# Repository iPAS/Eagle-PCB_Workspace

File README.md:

# Eagle-PCB Project Files

Sorry for inconvenience, I will make a description and index in near future.

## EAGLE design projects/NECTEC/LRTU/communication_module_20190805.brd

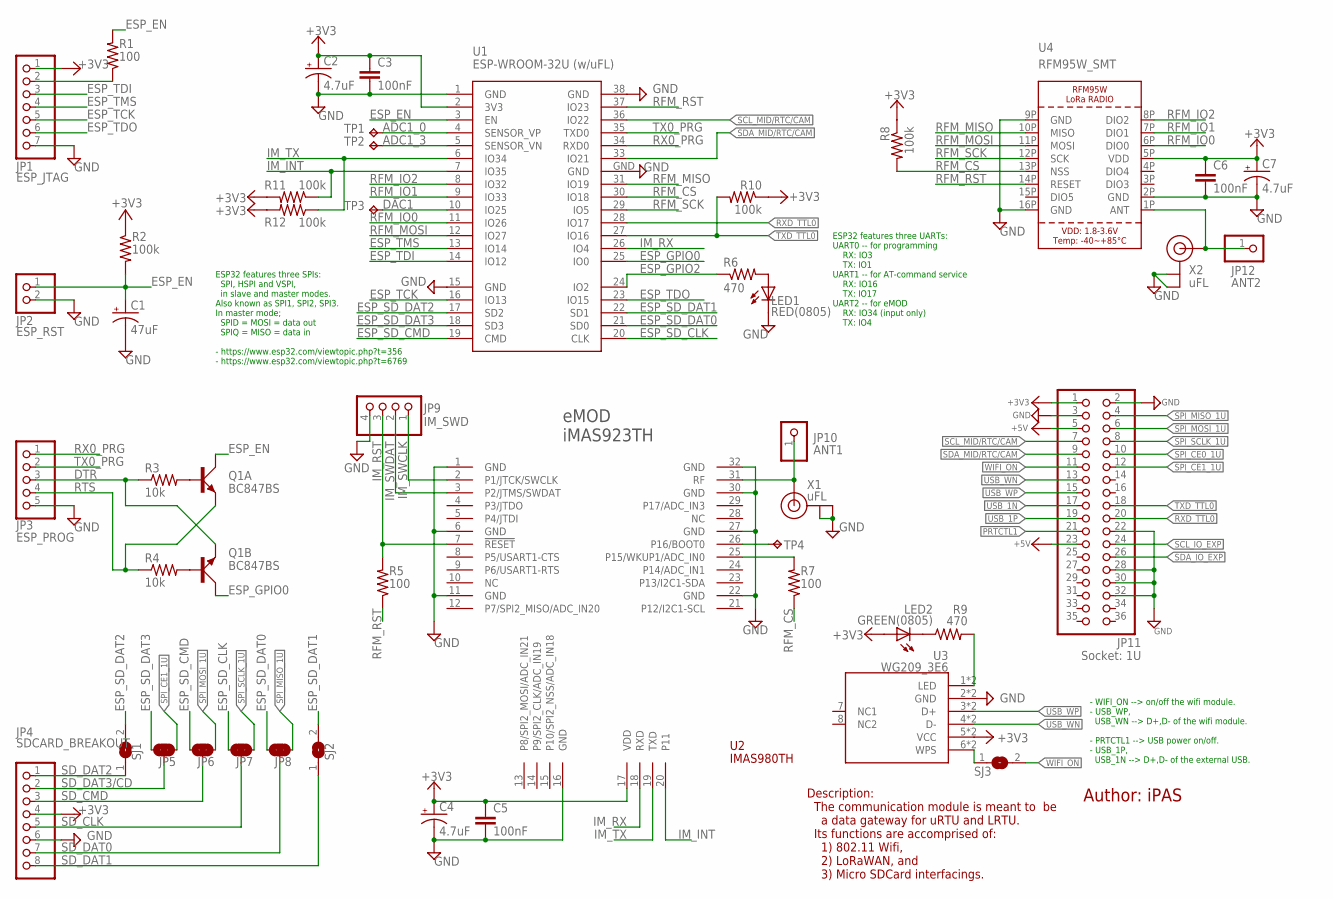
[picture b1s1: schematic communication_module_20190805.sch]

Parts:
C1: 47uF; RCL_150CLZ-1014
C2, C4, C7: 4.7uF; RCL_150CLZ-1014
C3, C5, C6: 100nF; RCL_C1206
JP1: ESP_JTAG; 1X07
JP2: ESP_RST; 1X02
JP3: ESP_PROG; 1X05
JP4: SDCARD_BREAKOUT; 1X08
JP5, JP6, JP7, JP8: JUMPER-SMT_3_NO_NO-SILK; SMT-JUMPER_3_NO_NO-SILK
JP9: IM_SWD; 1X04
JP10: ANT1; 1X01_ROUND
JP11: Socket: 1U; 2X18
JP12: ANT2; 1X01_ROUND
LED1: RED(0805); CHIP-LED0805
LED2: GREEN(0805); CHIP-LED0805
Q1: BC847BS; SOT363_PHILIPS
R1, R5, R7: 100; RCL_M0805
R2, R8, R10, R11, R12: 100k; RCL_M0805
R3, R4: 10k; RCL_M0805
R6, R9: 470; RCL_M0805
SJ1, SJ2, SJ3: SOLDERJUMPERREFLOW; SOLDERJUMPER_REFLOW
TP1, TP2, TP3, TP4: TPB1,27; B1,27
U1: ESP-WROOM-32U (w/uFL); ESP-WROOM-32
U2: IMAS980TH; IMAS923TH
U3: WG209_3E6; WG209
U4: RFM95W_SMT; RFMHCW_SMT
X1, X2: uFL; U.FL

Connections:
+3V3: C2.+, C3.1, C4.+, C5.1, C6.1, C7.+, JP1.1, JP4.4, JP11.1, LED2.A, R2.1, R8.1, R10.1, R11.2, R12.2, U1.2 (3V3), U2.17 (VDD), U3.5 (VCC), U3.5P (VCC), U4.5P (VDD)
+5V: JP11.5, JP11.23
ADC1_0: TP1.TP, U1.4 (SENSOR_VP)
ADC1_3: TP2.TP, U1.5 (SENSOR_VN)
ANT: JP12.1, U4.1P (ANT), X2.3 (SIGNAL)
DAC1: TP3.TP, U1.10 (IO25)
DTR: JP3.3, Q1.4 (E), R3.1
ESP_EN: C1.+, JP2.1, Q1.6 (C), R1.2, R2.2, U1.3 (EN)
ESP_GPIO0: Q1.3 (C), U1.25 (IO0)
ESP_GPIO2: R6.1, U1.24 (IO2)
ESP_SD_CLK: JP7.1, U1.20 (CLK)
ESP_SD_CMD: JP6.1, U1.19 (CMD)
ESP_SD_DAT0: JP8.1, U1.21 (SD0)
ESP_SD_DAT1: SJ2.2, U1.22 (SD1)
ESP_SD_DAT2: SJ1.2, U1.17 (SD2)
ESP_SD_DAT3: JP5.1, U1.18 (SD3)
ESP_TCK: JP1.5, U1.16 (IO13)
ESP_TDI: JP1.3, U1.14 (IO12)
ESP_TDO: JP1.6, U1.23 (IO15)
ESP_TMS: JP1.4, U1.13 (IO14)
GND: C1.-, C2.-, C3.2, C4.-, C5.2, C6.2, C7.-, JP1.7, JP2.2, JP3.5, JP4.6, JP9.4, JP11.2, JP11.3, JP11.22, JP11.28, JP11.30, JP11.32, LED1.C, U1.1 (GND), U1.15 (GND), U1.38 (GND), U1.GND, U2.1 (GND), U2.6 (GND), U2.11 (GND), U2.16 (GND), U2.22 (GND), U2.27 (GND), U2.30 (GND), U2.32 (GND), U3.2 (GND), U3.2P (GND), U4.2P (GND), U4.9P (GND), U4.16P (GND), X1.1 (GND), X1.2 (GND), X2.1 (GND), X2.2 (GND)
IM_INT: R11.1, U1.7 (IO35), U2.20 (P11)
IM_RST: JP9.3, R5.2, U2.7 (!RESET)
IM_RX: U1.26 (IO4), U2.18 (RXD)
IM_SWCLK: JP9.1, U2.2 (P1/JTCK/SWCLK)
IM_SWDAT: JP9.2, U2.3 (P2/JTMS/SWDAT)
IM_TX: R12.1, U1.6 (IO34), U2.19 (TXD)
unnamed: R9.2, U3.1 (LED), U3.1P (LED)
unnamed: SJ3.1, U3.6 (WPS), U3.6P (WPS)
unnamed: LED2.C, R9.1
unnamed: TP4.TP, U2.26 (P16/BOOT0)
unnamed: R7.2, U2.25 (P15/WKUP1/ADC_IN0)
unnamed: LED1.A, R6.2
unnamed: JP10.1, U2.31 (RF), X1.3 (SIGNAL)
unnamed: Q1.2 (B), R3.2
unnamed: Q1.5 (B), R4.2
unnamed: JP1.2, R1.1
PRTCTL1: JP11.21
RFM_CS: R7.1, R8.2, U1.30 (IO18), U4.13P (NSS)
RFM_IO0: U1.11 (IO26), U4.6P (DIO0)
RFM_IO1: U1.9 (IO33), U4.7P (DIO1)
RFM_IO2: U1.8 (IO32), U4.8P (DIO2)
RFM_MISO: U1.31 (IO19), U4.10P (MISO)
RFM_MOSI: U1.12 (IO27), U4.11P (MOSI)
RFM_RST: R5.1, U1.37 (IO23), U4.14P (RESET)
RFM_SCK: U1.29 (IO5), U4.12P (SCK)
RTS: JP3.4, Q1.1 (E), R4.1
RX0_PRG: JP3.1, U1.34 (RXD0)
RXD_TTL0: JP11.20, U1.28 (IO17)
SCL_IO_EXP: JP11.24
SCL_MID/RTC/CAM: JP11.7, U1.36 (IO22)
SDA_IO_EXP: JP11.26
SDA_MID/RTC/CAM: JP11.9, U1.33 (IO21)
SD_CLK: JP4.5, JP7.2
SD_CMD: JP4.3, JP6.2
SD_DAT0: JP4.7, JP8.2
SD_DAT1: JP4.8, SJ2.1
SD_DAT2: JP4.1, SJ1.1
SD_DAT3/CD: JP4.2, JP5.2
SPI_CE0_1U: JP11.10
SPI_CE1_1U: JP5.3, JP11.12
SPI_MISO_1U: JP8.3, JP11.4
SPI_MOSI_1U: JP6.3, JP11.6
SPI_SCLK_1U: JP7.3, JP11.8
TX0_PRG: JP3.2, U1.35 (TXD0)
TXD_TTL0: JP11.18, R10.2, U1.27 (IO16)
USB_1N: JP11.17
USB_1P: JP11.19
USB_WN: JP11.13, U3.4 (D-), U3.4P (D-)
USB_WP: JP11.15, U3.3 (D+), U3.3P (D+)
WIFI_ON: JP11.11, SJ3.2

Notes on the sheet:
ESP32 features three SPIs: SPI, HSPI and VSPI, in slave and master modes. Also known as SPI1, SPI2, SPI3. In master mode; SPID = MOSI = data out SPIQ = MISO = data in - https://www.esp32.com/viewtopic.php?t=356 - https://www.esp32.com/viewtopic.php?t=6769
- WIFI_ON --> on/off the wifi module. - USB_WP, USB_WN --> D+,D- of the wifi module. - PRTCTL1 --> USB power on/off. - USB_1P, USB_1N --> D+,D- of the external USB.
Description: The communication module is meant to be a data gateway for uRTU and LRTU. Its functions are accomprised of: 1) 802.11 Wifi, 2) LoRaWAN, and 3) Micro SDCard interfacings.
Author: iPAS
ESP32 features three UARTs: UART0 -- for programming RX: IO3 TX: IO1 UART1 -- for AT-command service RX: IO16 TX: IO17 UART2 -- for eMOD RX: IO34 (input only) TX: IO4

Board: 2 copper layers, 47 parts (0 on the bottom side), 65 nets, no tracks yet.

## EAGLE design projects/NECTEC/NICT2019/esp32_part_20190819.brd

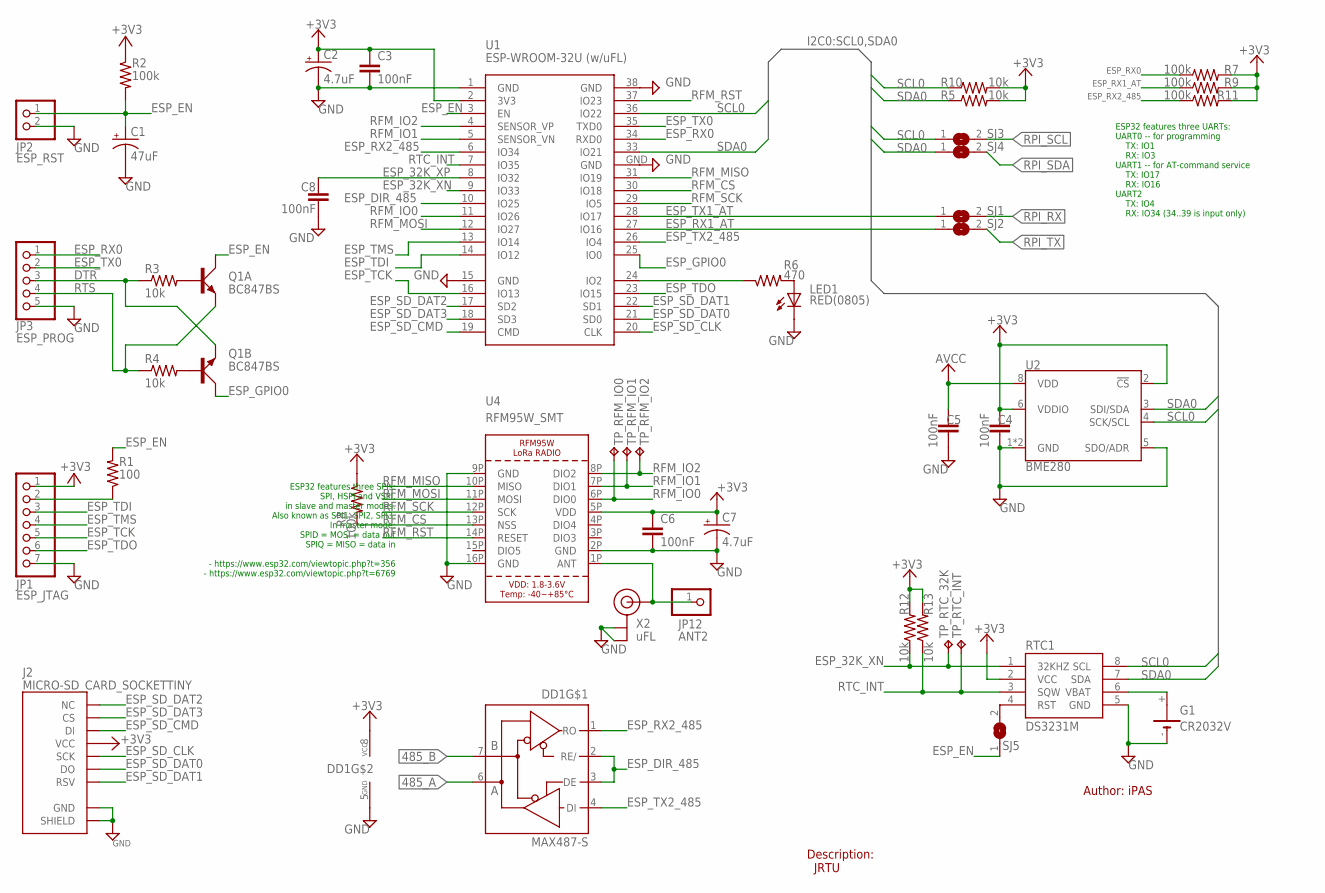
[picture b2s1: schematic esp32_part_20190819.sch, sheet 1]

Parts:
C1: 47uF; RCL_150CLZ-1014
C2, C7: 4.7uF; RCL_150CLZ-1014
C3, C4, C5, C6, C8: 100nF; RCL_C1206
DD1: MAX487-S; SO08
G1: CR2032V
J2: MICRO-SD_CARD_SOCKETTINY; MICROSD_TINY
JP1: ESP_JTAG; 1X07
JP2: ESP_RST; 1X02
JP3: ESP_PROG; 1X05
JP12: ANT2; 1X01_ROUND
LED1: RED(0805); CHIP-LED0805
Q1: BC847BS; SOT363_PHILIPS
R1: 100; RCL_M0805
R2, R7, R8, R9, R11: 100k; RCL_M0805
R3, R4, R5, R10, R12, R13: 10k; RCL_M0805
R6: 470; RCL_M0805
RTC1: DS3231M; SO08
SJ1, SJ2, SJ3, SJ4, SJ5: SOLDERJUMPERREFLOW; SOLDERJUMPER_REFLOW
TP_RFM_IO0, TP_RFM_IO1, TP_RFM_IO2: TPB1,27; B1,27
TP_RTC_32K: TPB1,27; B1,27
TP_RTC_INT: TPB1,27; B1,27
U1: ESP-WROOM-32U (w/uFL); ESP-WROOM-32
U2: BME280; LGA-8-2.5X2.5
U4: RFM95W_SMT; RFMHCW_SMT
X2: uFL; U.FL

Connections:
485_A: DD1.6 (A)
485_B: DD1.7 (B)
+3V3: C2.+, C3.1, C4.1, C6.1, C7.+, DD1.8 (VCC), J2.4 (VCC), JP1.1, R2.1, R5.2, R7.2, R8.1, R9.2, R10.2, R11.2, R12.2, R13.2, RTC1.2 (VCC), U1.2 (3V3), U2.2 (!CS), U2.6 (VDDIO), U4.5P (VDD); also elsewhere on the board
ANT: JP12.1, U4.1P (ANT), X2.3 (SIGNAL)
AVCC: C5.1, U2.8 (VDD)
DTR: JP3.3, Q1.4 (E), R3.1
ESP_32K_XN: R12.1, RTC1.1 (32KHZ), TP_RTC_32K.TP, U1.9 (IO33)
ESP_32K_XP: C8.2, U1.8 (IO32)
ESP_DIR_485: DD1.2 (RE/), DD1.3 (DE), U1.10 (IO25)
ESP_EN: C1.+, JP2.1, Q1.6 (C), R1.2, R2.2, SJ5.1, U1.3 (EN)
ESP_GPIO0: Q1.3 (C), U1.25 (IO0)
ESP_RX0: JP3.1, R7.1, U1.34 (RXD0)
ESP_RX1_AT: R9.1, SJ2.1, U1.27 (IO16)
ESP_RX2_485: DD1.1 (RO), R11.1, U1.6 (IO34)
ESP_SD_CLK: J2.5 (SCK), U1.20 (CLK)
ESP_SD_CMD: J2.3 (DI), U1.19 (CMD)
ESP_SD_DAT0: J2.7 (DO), U1.21 (SD0)
ESP_SD_DAT1: J2.1 (RSV), J2.8 (RSV), U1.22 (SD1)
ESP_SD_DAT2: J2.9 (NC), U1.17 (SD2)
ESP_SD_DAT3: J2.2 (CS), U1.18 (SD3)
ESP_TCK: JP1.5, U1.16 (IO13)
ESP_TDI: JP1.3, U1.14 (IO12)
ESP_TDO: JP1.6, U1.23 (IO15)
ESP_TMS: JP1.4, U1.13 (IO14)
ESP_TX0: JP3.2, U1.35 (TXD0)
ESP_TX1_AT: SJ1.1, U1.28 (IO17)
ESP_TX2_485: DD1.4 (DI), U1.26 (IO4)
GND: C1.-, C2.-, C3.2, C4.2, C5.2, C6.2, C7.-, C8.1, DD1.5 (GND), G1.-, J2.6 (GND), J2.GND1 (SHIELD), J2.GND2 (SHIELD), J2.GND3 (SHIELD), J2.GND4 (SHIELD), J2.GND5 (SHIELD), J2.GND6 (SHIELD), JP1.7, JP2.2, JP3.5, LED1.C, RTC1.5 (GND), U1.1 (GND), U1.15 (GND), U1.38 (GND), U1.GND, U2.1 (GND), U2.5 (SDO/ADR), U2.7 (GND), U4.2P (GND), U4.9P (GND), U4.16P (GND), X2.1 (GND), X2.2 (GND); also elsewhere on the board
unnamed: LED1.A, R6.2
unnamed: R6.1, U1.24 (IO2)
unnamed: G1.+, RTC1.6 (VBAT)
unnamed: RTC1.4 (RST), SJ5.2
unnamed: Q1.2 (B), R3.2
unnamed: Q1.5 (B), R4.2
unnamed: JP1.2, R1.1
RFM_CS: R8.2, U1.30 (IO18), U4.13P (NSS)
RFM_IO0: TP_RFM_IO0.TP, U1.11 (IO26), U4.6P (DIO0)
RFM_IO1: TP_RFM_IO1.TP, U1.5 (SENSOR_VN), U4.7P (DIO1)
RFM_IO2: TP_RFM_IO2.TP, U1.4 (SENSOR_VP), U4.8P (DIO2)
RFM_MISO: U1.31 (IO19), U4.10P (MISO)
RFM_MOSI: U1.12 (IO27), U4.11P (MOSI)
RFM_RST: U1.37 (IO23), U4.14P (RESET)
RFM_SCK: U1.29 (IO5), U4.12P (SCK)
RPI_RX: SJ1.2
RPI_SCL: SJ3.2
RPI_SDA: SJ4.2
RPI_TX: SJ2.2
RTC_INT: R13.1, RTC1.3 (SQW), TP_RTC_INT.TP, U1.7 (IO35)
RTS: JP3.4, Q1.1 (E), R4.1
SCL0: R10.1, RTC1.8 (SCL), SJ3.1, U1.36 (IO22), U2.4 (SCK/SCL)
SDA0: R5.1, RTC1.7 (SDA), SJ4.1, U1.33 (IO21), U2.3 (SDI/SDA)

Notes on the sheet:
ESP32 features three SPIs: SPI, HSPI and VSPI, in slave and master modes. Also known as SPI1, SPI2, SPI3. In master mode; SPID = MOSI = data out SPIQ = MISO = data in - https://www.esp32.com/viewtopic.php?t=356 - https://www.esp32.com/viewtopic.php?t=6769
Description: JRTU
Author: iPAS
ESP32 features three UARTs: UART0 -- for programming TX: IO1 RX: IO3 UART1 -- for AT-command service TX: IO17 RX: IO16 UART2 TX: IO4 RX: IO34 (34..39 is input only)

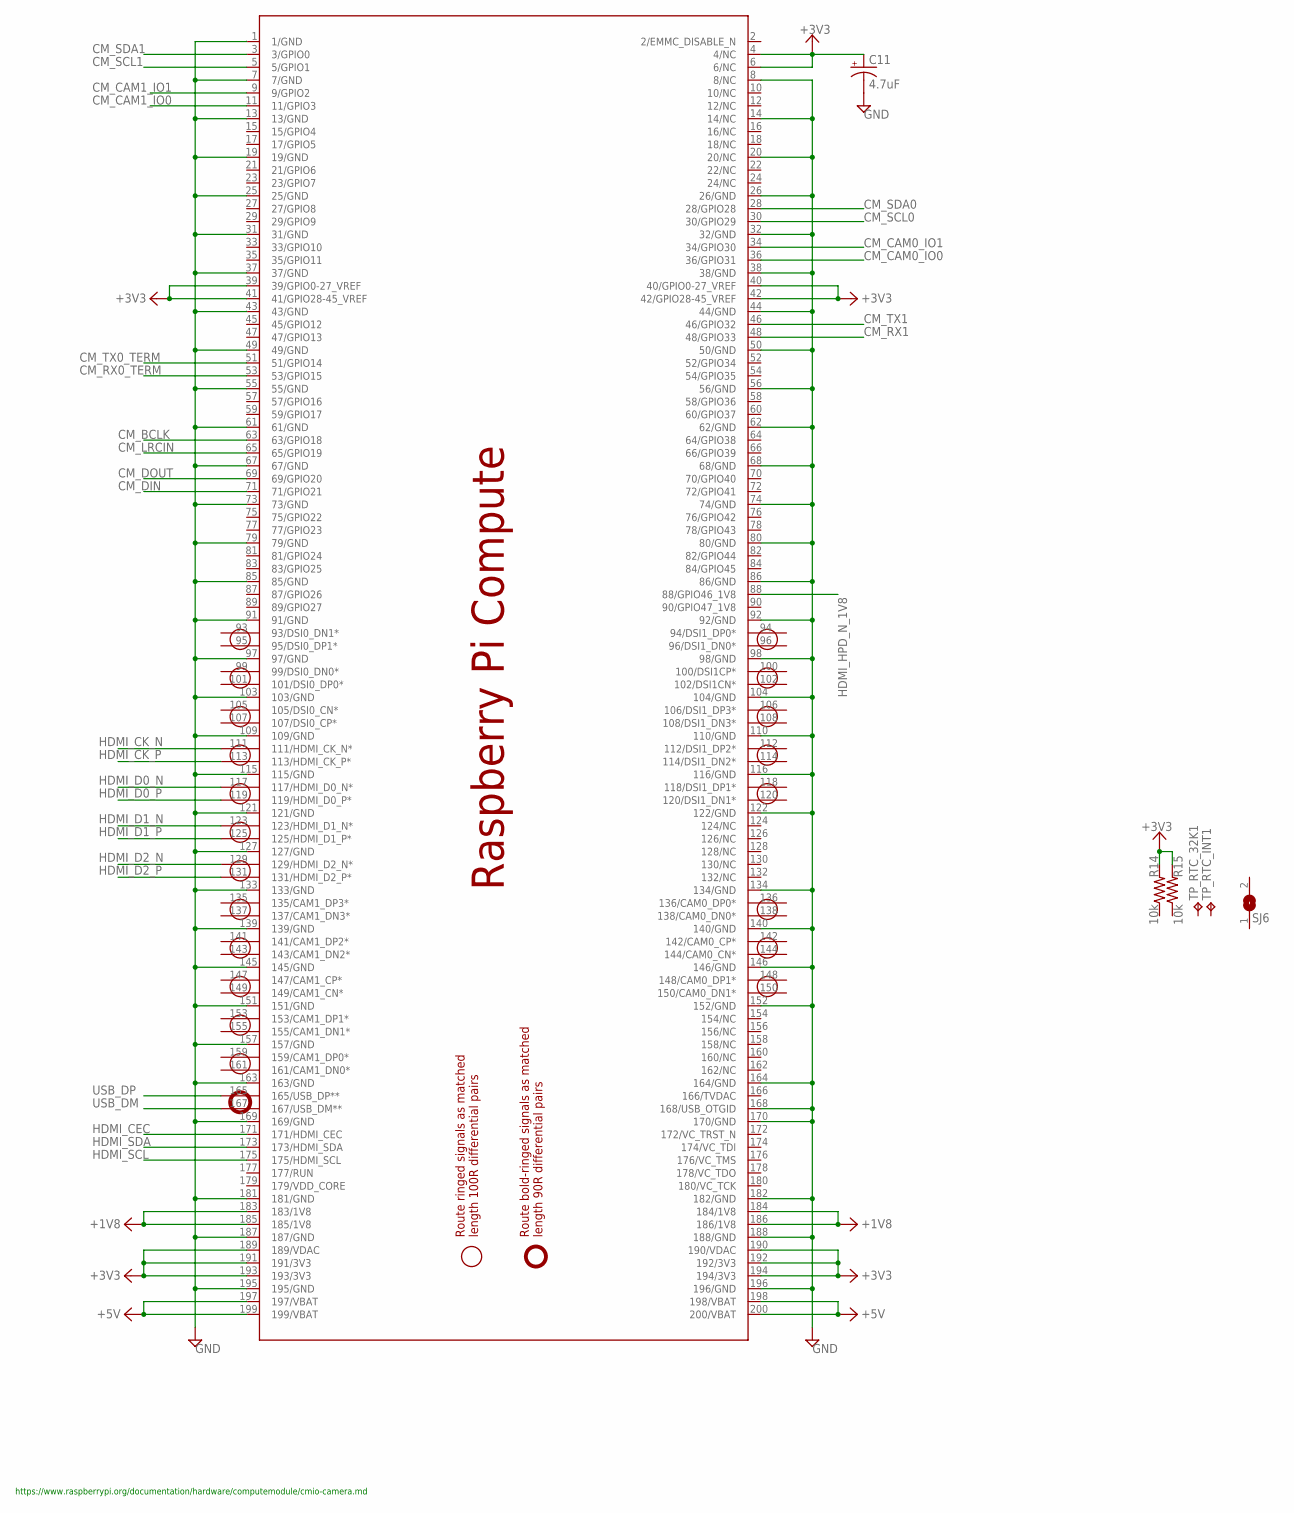
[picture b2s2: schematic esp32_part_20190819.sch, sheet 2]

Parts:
C11: 4.7uF; RCL_150CLZ-1014
R14, R15: 10k; RCL_M0805
SJ6: SOLDERJUMPERREFLOW; SOLDERJUMPER_REFLOW
SODIMM: RPI_COMPUTE
TP_RTC_32K1: TPB1,27; B1,27
TP_RTC_INT1: TPB1,27; B1,27

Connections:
+3V3: C11.+, R14.2, R15.2, SODIMM.4 (4/NC), SODIMM.6 (6/NC), SODIMM.39 (39/GPIO0-27_VREF), SODIMM.40 (40/GPIO0-27_VREF), SODIMM.41 (41/GPIO28-45_VREF), SODIMM.42 (42/GPIO28-45_VREF), SODIMM.183 (183/1V8), SODIMM.184 (184/1V8), SODIMM.185 (185/1V8), SODIMM.186 (186/1V8), SODIMM.189 (189/VDAC), SODIMM.190 (190/VDAC), SODIMM.191 (191/3V3), SODIMM.192 (192/3V3), SODIMM.193 (193/3V3), SODIMM.194 (194/3V3); also elsewhere on the board
+5V: SODIMM.197 (197/VBAT), SODIMM.198 (198/VBAT), SODIMM.199 (199/VBAT), SODIMM.200 (200/VBAT)
CM_BCLK: SODIMM.63 (63/GPIO18)
CM_CAM0_IO0: SODIMM.36 (36/GPIO31)
CM_CAM0_IO1: SODIMM.34 (34/GPIO30)
CM_CAM1_IO0: SODIMM.11 (11/GPIO3)
CM_CAM1_IO1: SODIMM.9 (9/GPIO2)
CM_DIN: SODIMM.71 (71/GPIO21)
CM_DOUT: SODIMM.69 (69/GPIO20)
CM_LRCIN: SODIMM.65 (65/GPIO19)
CM_RX0_TERM: SODIMM.53 (53/GPIO15)
CM_RX1: SODIMM.48 (48/GPIO33)
CM_SCL0: SODIMM.30 (30/GPIO29)
CM_SCL1: SODIMM.5 (5/GPIO1)
CM_SDA0: SODIMM.28 (28/GPIO28)
CM_SDA1: SODIMM.3 (3/GPIO0)
CM_TX0_TERM: SODIMM.51 (51/GPIO14)
CM_TX1: SODIMM.46 (46/GPIO32)
GND: C11.-, SODIMM.1 (1/GND), SODIMM.7 (7/GND), SODIMM.8 (8/NC), SODIMM.13 (13/GND), SODIMM.14 (14/NC), SODIMM.19 (19/GND), SODIMM.20 (20/NC), SODIMM.25 (25/GND), SODIMM.26 (26/GND), SODIMM.31 (31/GND), SODIMM.32 (32/GND), SODIMM.37 (37/GND), SODIMM.38 (38/GND), SODIMM.43 (43/GND), SODIMM.44 (44/GND), SODIMM.49 (49/GND), SODIMM.50 (50/GND), SODIMM.55 (55/GND), SODIMM.56 (56/GND), SODIMM.61 (61/GND), SODIMM.62 (62/GND), SODIMM.67 (67/GND), SODIMM.68 (68/GND), SODIMM.73 (73/GND), SODIMM.74 (74/GND), SODIMM.79 (79/GND), SODIMM.80 (80/GND), SODIMM.85 (85/GND), SODIMM.86 (86/GND), SODIMM.91 (91/GND), SODIMM.92 (92/GND), SODIMM.97 (97/GND), SODIMM.98 (98/GND), SODIMM.103 (103/GND), SODIMM.104 (104/GND), SODIMM.109 (109/GND), SODIMM.110 (110/GND), SODIMM.115 (115/GND), SODIMM.116 (116/GND), SODIMM.121 (121/GND), SODIMM.122 (122/GND), SODIMM.127 (127/GND), SODIMM.133 (133/GND), SODIMM.134 (134/GND), SODIMM.139 (139/GND), SODIMM.140 (140/GND), SODIMM.145 (145/GND), SODIMM.146 (146/GND), SODIMM.151 (151/GND), SODIMM.152 (152/GND), SODIMM.157 (157/GND), SODIMM.163 (163/GND), SODIMM.164 (164/GND), SODIMM.168 (168/USB_OTGID), SODIMM.169 (169/GND), SODIMM.170 (170/GND), SODIMM.181 (181/GND), SODIMM.182 (182/GND), SODIMM.187 (187/GND), SODIMM.188 (188/GND), SODIMM.195 (195/GND), SODIMM.196 (196/GND); also elsewhere on the board
HDMI_CEC: SODIMM.171 (171/HDMI_CEC)
HDMI_CK_N: SODIMM.111 (111/HDMI_CK_N*)
HDMI_CK_P: SODIMM.113 (113/HDMI_CK_P*)
HDMI_D0_N: SODIMM.117 (117/HDMI_D0_N*)
HDMI_D0_P: SODIMM.119 (119/HDMI_D0_P*)
HDMI_D1_N: SODIMM.123 (123/HDMI_D1_N*)
HDMI_D1_P: SODIMM.125 (125/HDMI_D1_P*)
HDMI_D2_N: SODIMM.129 (129/HDMI_D2_N*)
HDMI_D2_P: SODIMM.131 (131/HDMI_D2_P*)
HDMI_HPD_N_1V8: SODIMM.88 (88/GPIO46_1V8)
HDMI_SCL: SODIMM.175 (175/HDMI_SCL)
HDMI_SDA: SODIMM.173 (173/HDMI_SDA)
USB_DM: SODIMM.167 (167/USB_DM**)
USB_DP: SODIMM.165 (165/USB_DP**)

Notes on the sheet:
https://www.raspberrypi.org/documentation/hardware/computemodule/cmio-camera.md

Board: 2 copper layers, 52 parts (0 on the bottom side), 46 nets, no tracks yet.

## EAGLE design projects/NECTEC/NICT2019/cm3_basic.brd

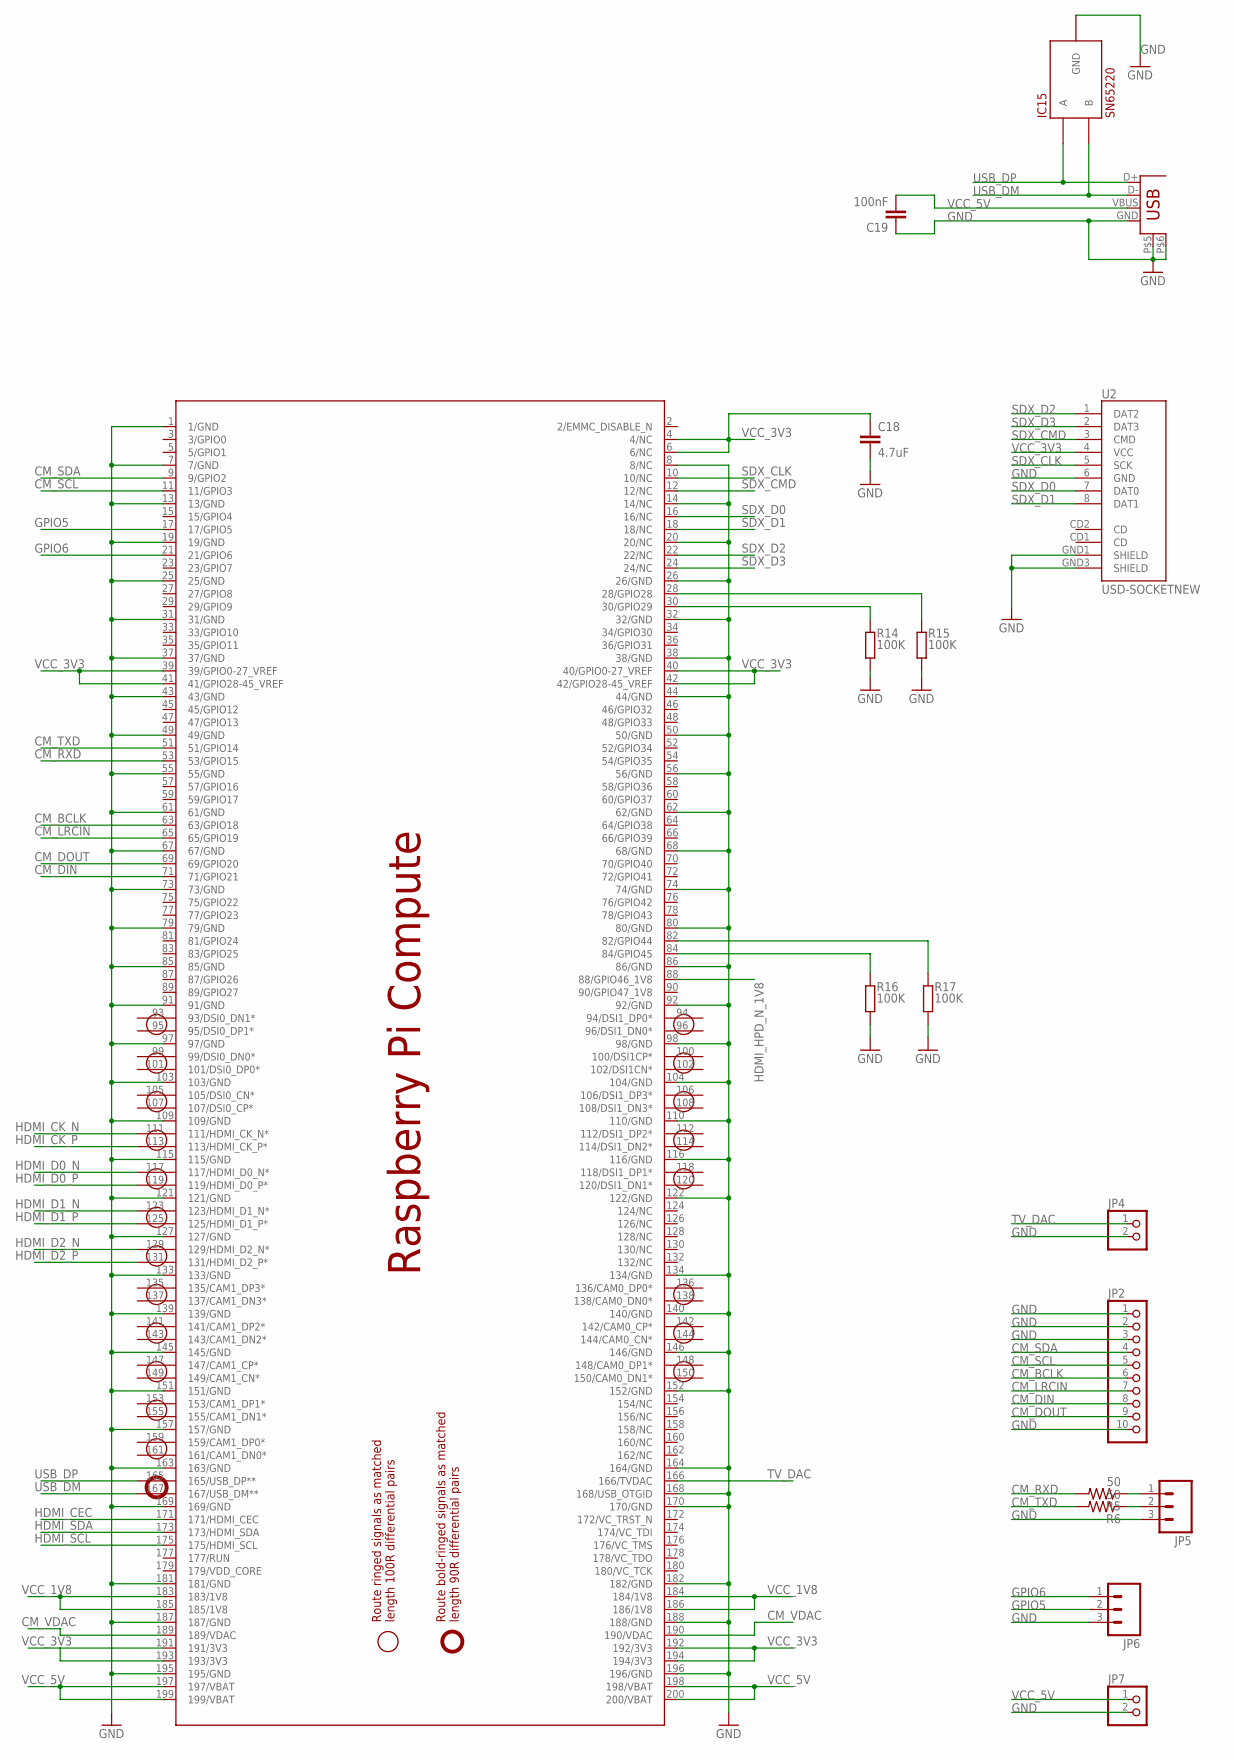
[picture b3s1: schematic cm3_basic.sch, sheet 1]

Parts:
C18: 4.7uF; C1608
C19: 100nF; 0603-CAP
IC15: SN65220; SOT23-6L
JP2: PINHD-1X10; 1X10
JP3: USB-A; USB-A-S-NOSILK-FEMALE
JP4, JP7: PINHD-1X2; 1X02
JP5, JP6: M03LOCK_LONGPADS; 1X03_LOCK_LONGPADS
R5, R6: 50; 0603-RES
R14, R15, R16, R17: 100K; R0603
SODIMM: RPI_COMPUTE
U2: USD-SOCKETNEW; MICRO-SD-SOCKET-PP

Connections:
CM_BCLK: JP2.6, SODIMM.63 (63/GPIO18)
CM_DIN: JP2.8, SODIMM.71 (71/GPIO21)
CM_DOUT: JP2.9, SODIMM.69 (69/GPIO20)
CM_LRCIN: JP2.7, SODIMM.65 (65/GPIO19)
CM_RXD: R5.2, SODIMM.53 (53/GPIO15)
CM_SCL: JP2.5, SODIMM.11 (11/GPIO3)
CM_SDA: JP2.4, SODIMM.9 (9/GPIO2)
CM_TXD: R6.2, SODIMM.51 (51/GPIO14)
CM_VDAC: SODIMM.189 (189/VDAC), SODIMM.190 (190/VDAC); also elsewhere on the board
GND: C18.2, C19.1, IC15.2 (GND), IC15.5 (GND), JP2.1, JP2.2, JP2.3, JP2.10, JP3.GND, JP3.P$5 (SHIELD1), JP3.P$6 (SHIELD2), JP4.2, JP5.3, JP6.3, JP7.2, R14.1, R15.1, R16.1, R17.1, SODIMM.1 (1/GND), SODIMM.7 (7/GND), SODIMM.8 (8/NC), SODIMM.13 (13/GND), SODIMM.14 (14/NC), SODIMM.19 (19/GND), SODIMM.20 (20/NC), SODIMM.25 (25/GND), SODIMM.26 (26/GND), SODIMM.31 (31/GND), SODIMM.32 (32/GND), SODIMM.37 (37/GND), SODIMM.38 (38/GND), SODIMM.43 (43/GND), SODIMM.44 (44/GND), SODIMM.49 (49/GND), SODIMM.50 (50/GND), SODIMM.55 (55/GND), SODIMM.56 (56/GND), SODIMM.61 (61/GND), SODIMM.62 (62/GND), SODIMM.67 (67/GND), SODIMM.68 (68/GND), SODIMM.73 (73/GND), SODIMM.74 (74/GND), SODIMM.79 (79/GND), SODIMM.80 (80/GND), SODIMM.85 (85/GND), SODIMM.86 (86/GND), SODIMM.91 (91/GND), SODIMM.92 (92/GND), SODIMM.97 (97/GND), SODIMM.98 (98/GND), SODIMM.103 (103/GND), SODIMM.104 (104/GND), SODIMM.109 (109/GND), SODIMM.110 (110/GND), SODIMM.115 (115/GND), SODIMM.116 (116/GND), SODIMM.121 (121/GND), SODIMM.122 (122/GND), SODIMM.127 (127/GND), SODIMM.133 (133/GND), SODIMM.134 (134/GND), SODIMM.139 (139/GND), SODIMM.140 (140/GND), SODIMM.145 (145/GND), SODIMM.146 (146/GND), SODIMM.151 (151/GND), SODIMM.152 (152/GND), SODIMM.157 (157/GND), SODIMM.163 (163/GND), SODIMM.164 (164/GND), SODIMM.168 (168/USB_OTGID), SODIMM.169 (169/GND), SODIMM.170 (170/GND), SODIMM.181 (181/GND), SODIMM.182 (182/GND), SODIMM.187 (187/GND), SODIMM.188 (188/GND), SODIMM.195 (195/GND), SODIMM.196 (196/GND), U2.6 (GND), U2.GND1 (SHIELD), U2.GND3 (SHIELD); also elsewhere on the board
GPIO5: JP6.2, SODIMM.17 (17/GPIO5)
GPIO6: JP6.1, SODIMM.21 (21/GPIO6)
HDMI_CEC: SODIMM.171 (171/HDMI_CEC); also elsewhere on the board
HDMI_CK_N: SODIMM.111 (111/HDMI_CK_N*); also elsewhere on the board
HDMI_CK_P: SODIMM.113 (113/HDMI_CK_P*); also elsewhere on the board
HDMI_D0_N: SODIMM.117 (117/HDMI_D0_N*); also elsewhere on the board
HDMI_D0_P: SODIMM.119 (119/HDMI_D0_P*); also elsewhere on the board
HDMI_D1_N: SODIMM.123 (123/HDMI_D1_N*); also elsewhere on the board
HDMI_D1_P: SODIMM.125 (125/HDMI_D1_P*); also elsewhere on the board
HDMI_D2_N: SODIMM.129 (129/HDMI_D2_N*); also elsewhere on the board
HDMI_D2_P: SODIMM.131 (131/HDMI_D2_P*); also elsewhere on the board
HDMI_HPD_N_1V8: SODIMM.88 (88/GPIO46_1V8); also elsewhere on the board
HDMI_SCL: SODIMM.175 (175/HDMI_SCL); also elsewhere on the board
HDMI_SDA: SODIMM.173 (173/HDMI_SDA); also elsewhere on the board
unnamed: JP5.1, R5.1
unnamed: JP5.2, R6.1
unnamed: R16.2, SODIMM.84 (84/GPIO45)
unnamed: R15.2, SODIMM.28 (28/GPIO28)
unnamed: R14.2, SODIMM.30 (30/GPIO29)
unnamed: R17.2, SODIMM.82 (82/GPIO44)
SDX_CLK: SODIMM.10 (10/NC), U2.5 (SCK)
SDX_CMD: SODIMM.12 (12/NC), U2.3 (CMD)
SDX_D0: SODIMM.16 (16/NC), U2.7 (DAT0)
SDX_D1: SODIMM.18 (18/NC), U2.8 (DAT1)
SDX_D2: SODIMM.22 (22/NC), U2.1 (DAT2)
SDX_D3: SODIMM.24 (24/NC), U2.2 (DAT3)
TV_DAC: JP4.1, SODIMM.166 (166/TVDAC)
USB_DM: IC15.4 (B), JP3.D-, SODIMM.167 (167/USB_DM**)
USB_DP: IC15.6 (A), JP3.D+, SODIMM.165 (165/USB_DP**)
VCC_1V8: SODIMM.183 (183/1V8), SODIMM.184 (184/1V8), SODIMM.185 (185/1V8), SODIMM.186 (186/1V8); also elsewhere on the board
VCC_3V3: C18.1, SODIMM.4 (4/NC), SODIMM.6 (6/NC), SODIMM.39 (39/GPIO0-27_VREF), SODIMM.40 (40/GPIO0-27_VREF), SODIMM.41 (41/GPIO28-45_VREF), SODIMM.42 (42/GPIO28-45_VREF), SODIMM.191 (191/3V3), SODIMM.192 (192/3V3), SODIMM.193 (193/3V3), SODIMM.194 (194/3V3), U2.4 (VCC); also elsewhere on the board
VCC_5V: C19.2, JP3.VBUS, JP7.1, SODIMM.197 (197/VBAT), SODIMM.198 (198/VBAT), SODIMM.199 (199/VBAT), SODIMM.200 (200/VBAT); also elsewhere on the board

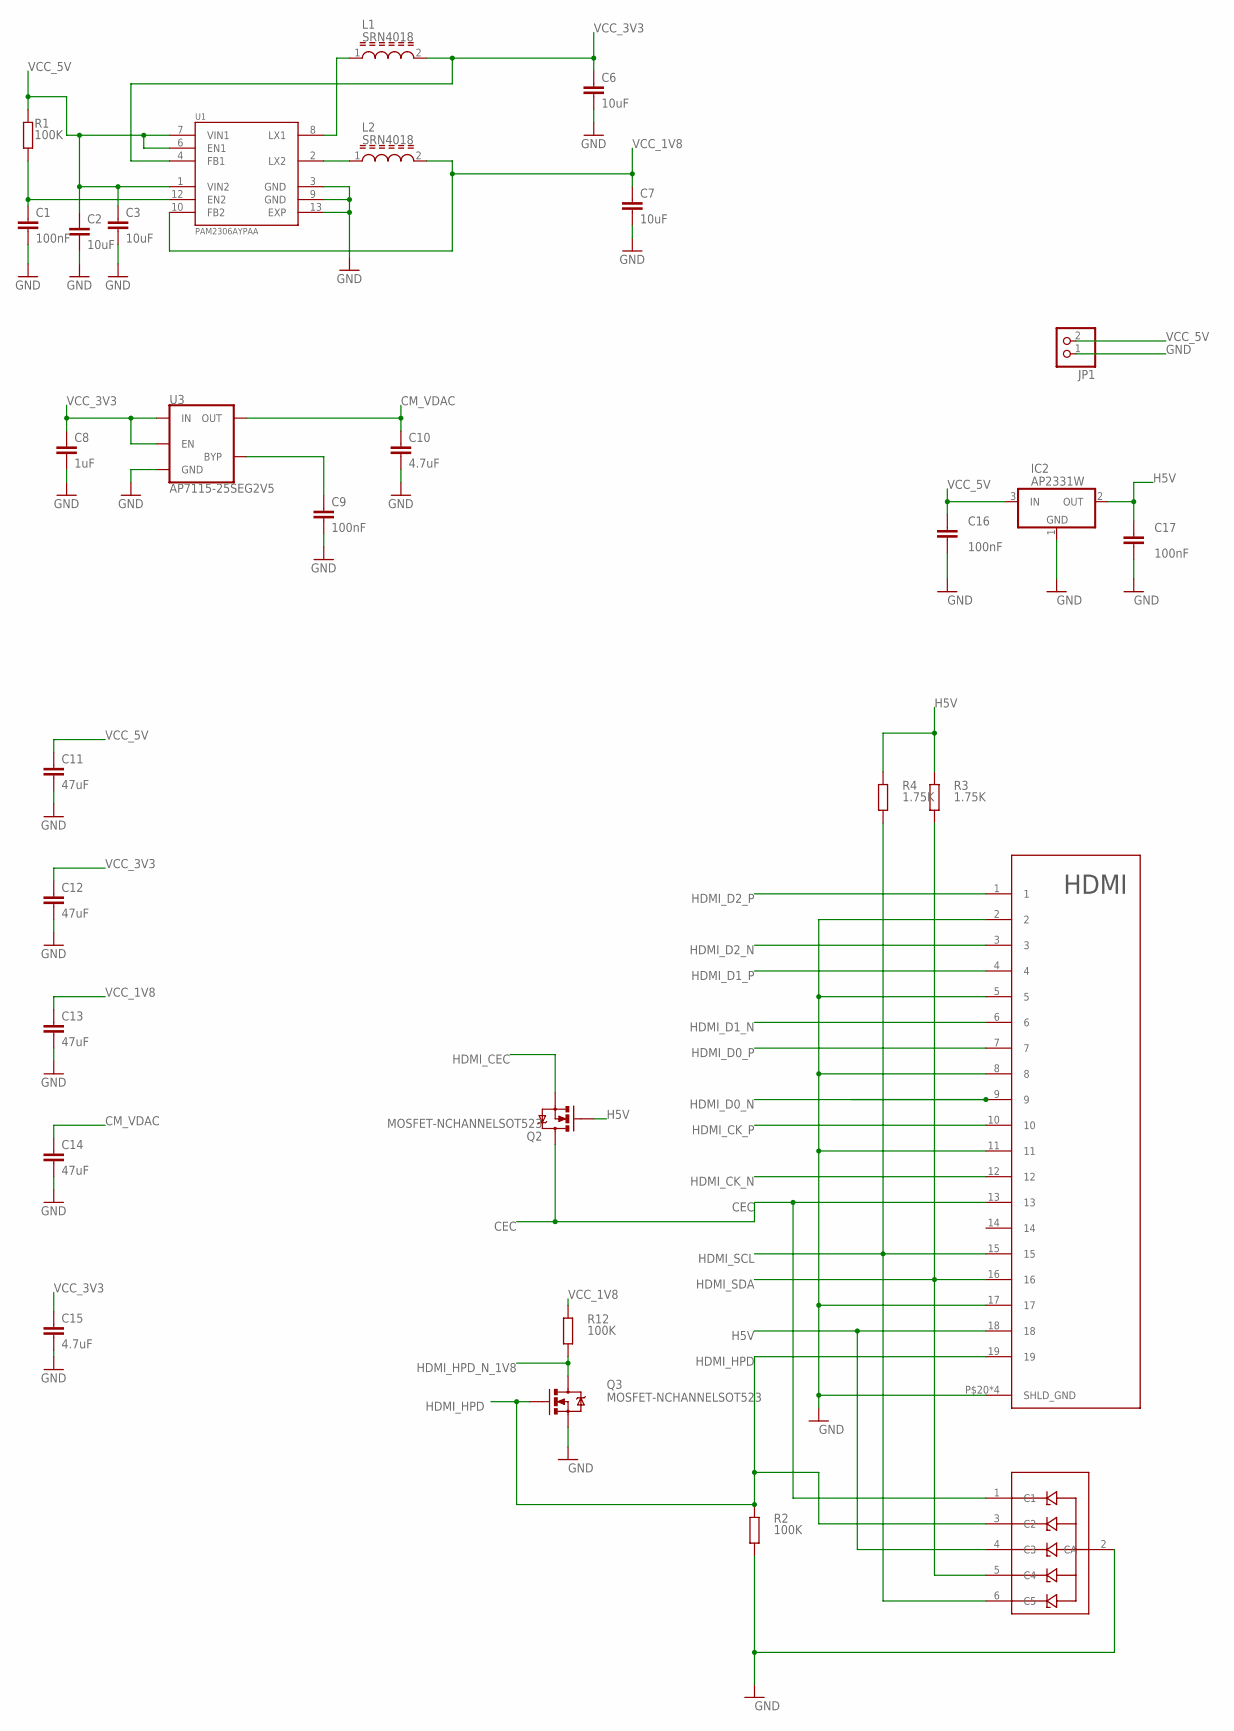
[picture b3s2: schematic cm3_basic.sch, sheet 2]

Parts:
C1, C9, C16, C17: 100nF; C0603
C2, C3, C6, C7: 10uF; C0805
C8: 1uF; C0603
C10, C15: 4.7uF; C0603
C11, C12, C13, C14: 47uF; C3216
IC1: PESD3V3L5UYSOT363; SOT363-INFINION
IC2: AP2331W; SOT23
JP1: PINHD-1X2; 1X02
L1, L2: SRN4018; INDP4040X180N
Q2, Q3: MOSFET-NCHANNELSOT523; SOT523
R1, R2, R12: 100K; R0603
R3, R4: 1.75K; R0603
U1: PAM2306AYPAA; SON45P300X300X80-13N
U3: AP7115-25SEG2V5; SC70
U4: HDMI

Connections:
CEC: IC1.1 (C1), Q2.3 (D), U4.13
CM_VDAC: C10.1, C14.1, U3.5 (OUT); also elsewhere on the board
GND: C1.2, C2.2, C3.2, C6.2, C7.2, C8.2, C9.2, C10.2, C11.2, C12.2, C13.2, C14.2, C15.2, C16.2, C17.2, IC1.2 (CA), IC2.1 (GND), JP1.1, Q3.2 (S), R2.1, U1.3 (GND), U1.9 (GND), U1.13 (EXP), U3.2 (GND), U4.2, U4.5, U4.8, U4.11, U4.17, U4.P$20 (SHLD_GND), U4.P$21 (SHLD_GND), U4.P$22 (SHLD_GND), U4.P$23 (SHLD_GND); also elsewhere on the board
H5V: C17.1, IC1.4 (C3), IC2.2 (OUT), Q2.1 (G), R3.2, R4.2, U4.18
HDMI_CEC: Q2.2 (S); also elsewhere on the board
HDMI_CK_N: U4.12; also elsewhere on the board
HDMI_CK_P: U4.10; also elsewhere on the board
HDMI_D0_N: U4.9; also elsewhere on the board
HDMI_D0_P: U4.7; also elsewhere on the board
HDMI_D1_N: U4.6; also elsewhere on the board
HDMI_D1_P: U4.4; also elsewhere on the board
HDMI_D2_N: U4.3; also elsewhere on the board
HDMI_D2_P: U4.1; also elsewhere on the board
HDMI_HPD: IC1.3 (C2), Q3.1 (G), R2.2, U4.19
HDMI_HPD_N_1V8: Q3.3 (D), R12.1; also elsewhere on the board
HDMI_SCL: IC1.6 (C5), R4.1, U4.15; also elsewhere on the board
HDMI_SDA: IC1.5 (C4), R3.1, U4.16; also elsewhere on the board
unnamed: L1.1, U1.8 (LX1)
unnamed: C1.1, R1.1, U1.12 (EN2)
unnamed: L2.1, U1.2 (LX2)
unnamed: C9.1, U3.4 (BYP)
VCC_1V8: C7.1, C13.1, L2.2, R12.2, U1.10 (FB2); also elsewhere on the board
VCC_3V3: C6.1, C8.1, C12.1, C15.1, L1.2, U1.4 (FB1), U3.1 (IN), U3.3 (EN); also elsewhere on the board
VCC_5V: C2.1, C3.1, C11.1, C16.1, IC2.3 (IN), JP1.2, R1.2, U1.1 (VIN2), U1.6 (EN1), U1.7 (VIN1); also elsewhere on the board

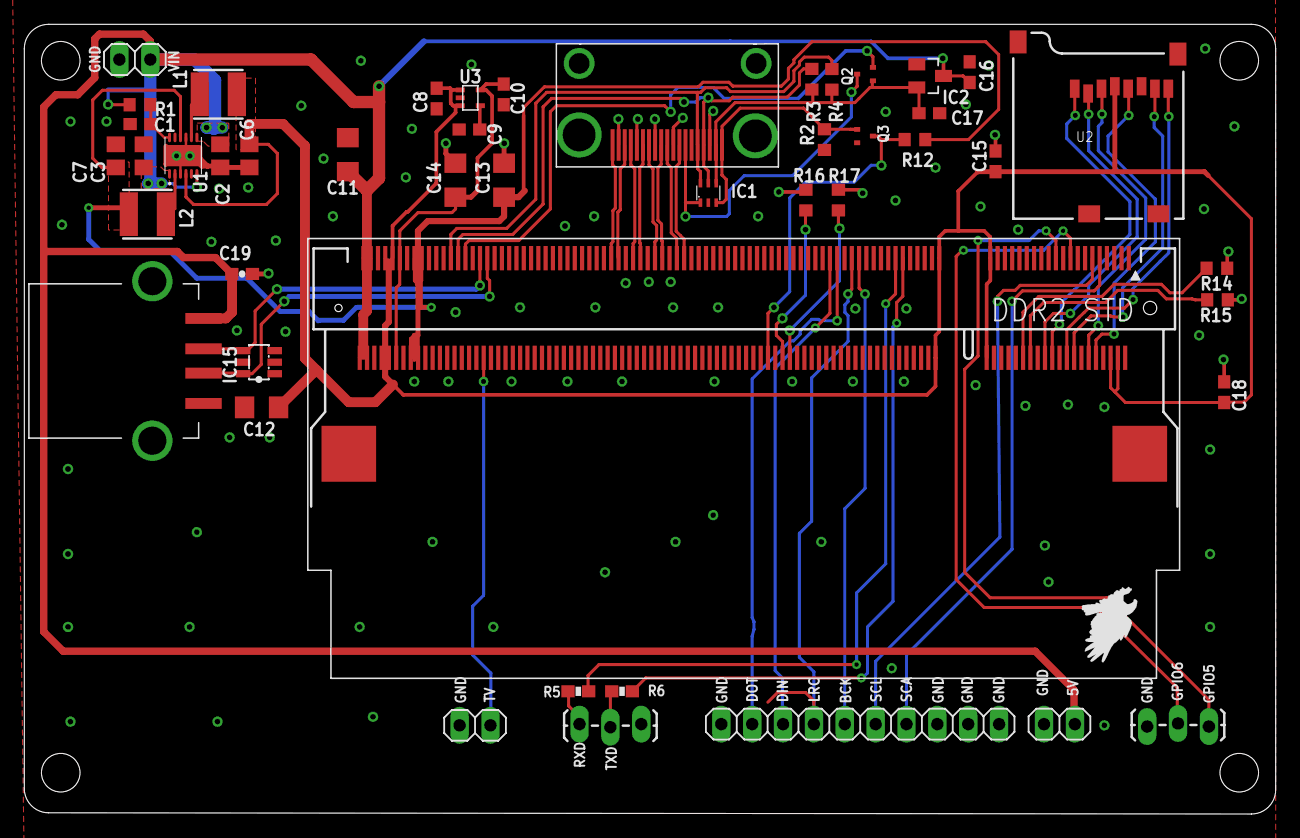
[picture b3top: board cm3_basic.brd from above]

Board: 2 copper layers, 103.0 x 65.0 mm, 47 parts (0 on the bottom side), 49 nets.

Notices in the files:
parts and their libraries:
diy-modules: Released under the Creative Commons Attribution 4.0 International License: http://creativecommons.org/licenses/by/4.0
SparkFun-Connectors: Licensing: CC v3.0 Share-Alike You are welcome to use this library for commercial purposes.
